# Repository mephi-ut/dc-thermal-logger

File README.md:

LICENSE: WTFPLv2

The purpose of this project is to monitor themperature in a lot of points of DC.

Operating principle:

Collector schematic:

Thermal sensor schematic:

A model photo:

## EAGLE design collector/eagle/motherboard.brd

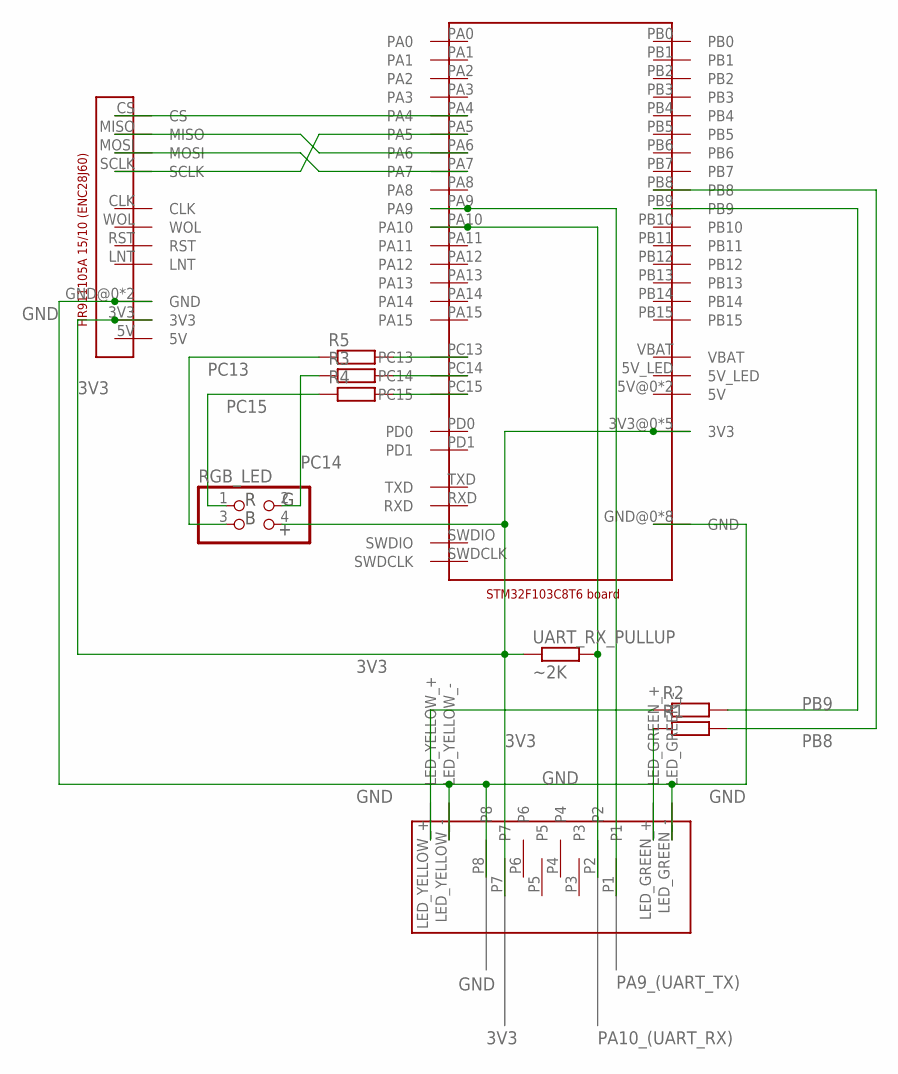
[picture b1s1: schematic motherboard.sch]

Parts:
R1, R2, R3, R4, R5: R-EU_R1206; R1206
RGB_LED: PINHD-2X2; 2X02
U$1: HANRUN_HR911105A_15/10
U$2: STM32F103C8T6_BOARD_BLACK
U$3: RJHSE-5481_(RJ45)
UART_RX_PULLUP: ~2K; R1206

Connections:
3V3: RGB_LED.4, U$1.3V3, U$2.3V3@0 (3V3), U$2.3V3@1 (3V3), U$2.3V3@2 (3V3), U$2.3V3@3 (3V3), U$2.3V3@4 (3V3), U$3.P7, UART_RX_PULLUP.1
GND: U$1.GND@0 (GND), U$1.GND@1 (GND), U$2.GND@0 (GND), U$2.GND@1 (GND), U$2.GND@2 (GND), U$2.GND@3 (GND), U$2.GND@4 (GND), U$2.GND@5 (GND), U$2.GND@6 (GND), U$2.GND@7 (GND), U$3.LED_GREEN_-, U$3.LED_YELLOW_-, U$3.P8
unnamed: U$1.CS, U$2.PA4
unnamed: U$1.SCLK, U$2.PA5
unnamed: U$1.MISO, U$2.PA6
unnamed: U$1.MOSI, U$2.PA7
unnamed: R1.1, U$3.LED_GREEN_+
unnamed: R4.2, U$2.PC15
unnamed: R3.2, U$2.PC14
unnamed: R5.2, U$2.PC13
PA9_(UART_TX): U$2.PA9, U$3.P1
PA10_(UART_RX): U$2.PA10, U$3.P2, UART_RX_PULLUP.2
PB8: R1.2, U$2.PB8
PB9: R2.2, U$2.PB9
PB9R: R2.1, U$3.LED_YELLOW_+
PC13: R5.1, RGB_LED.3
PC14: R3.1, RGB_LED.2
PC15: R4.1, RGB_LED.1

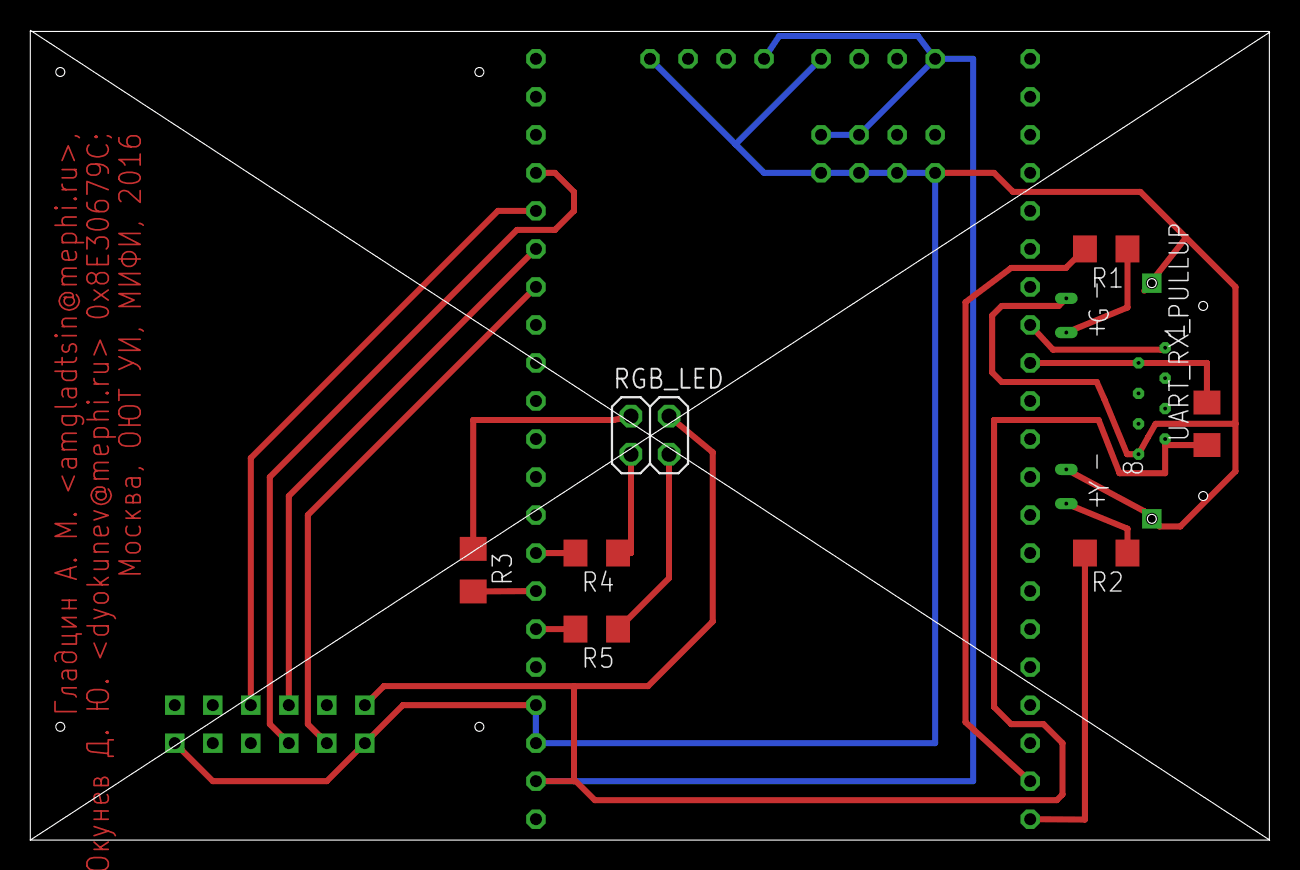
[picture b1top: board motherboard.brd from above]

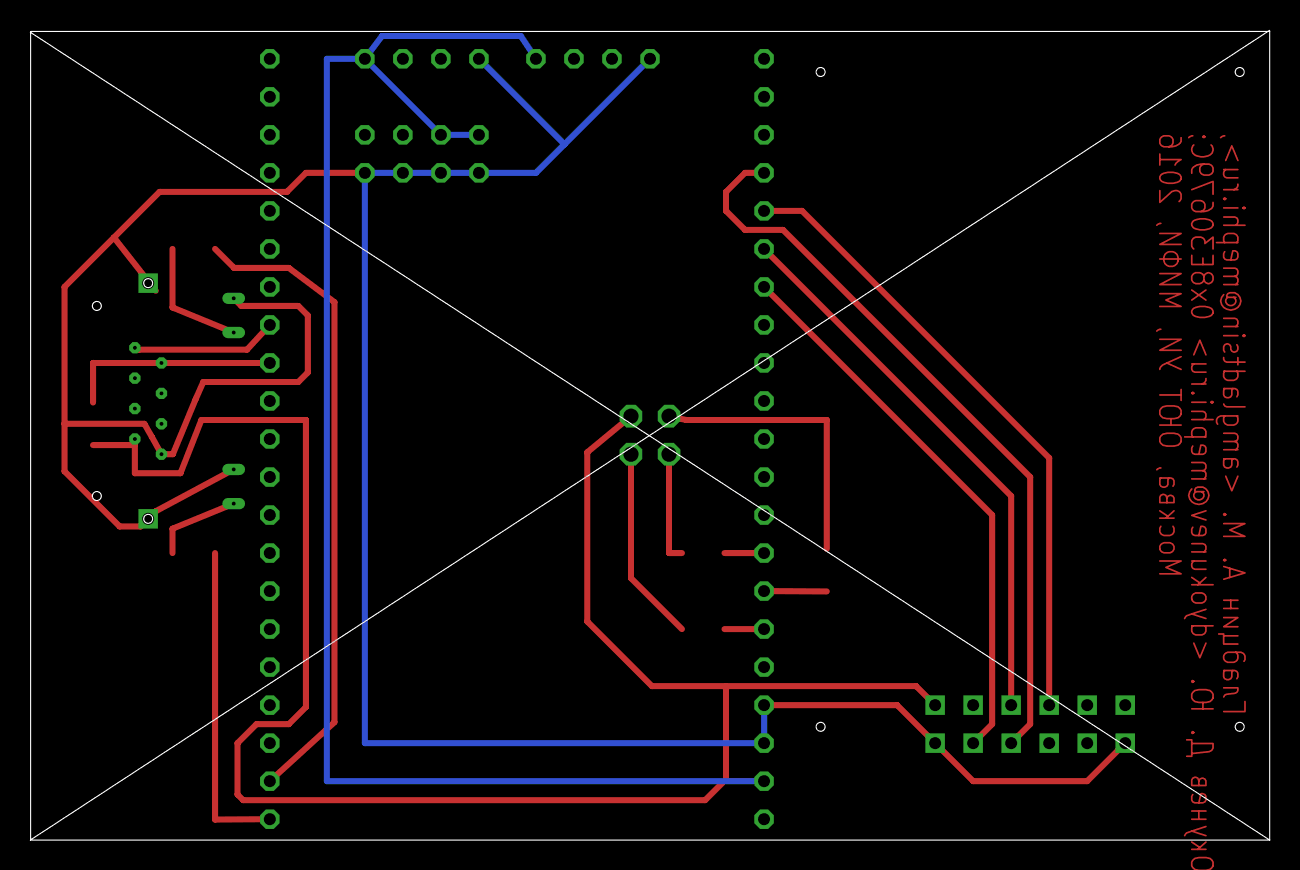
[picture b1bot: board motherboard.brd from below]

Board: 2 copper layers, 82.8 x 54.1 mm, 10 parts (2 on the bottom side), 18 nets.

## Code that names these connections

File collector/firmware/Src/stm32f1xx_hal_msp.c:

/**
  ******************************************************************************
  * File Name          : stm32f1xx_hal_msp.c
  * Description        : This file provides code for the MSP Initialization 
  *                      and de-Initialization codes.
  ******************************************************************************
  *
  * COPYRIGHT(c) 2016 STMicroelectronics
  *
  * Redistribution and use in source and binary forms, with or without modification,
  * are permitted provided that the following conditions are met:
  *   1. Redistributions of source code must retain the above copyright notice,
  *      this list of conditions and the following disclaimer.
  *   2. Redistributions in binary form must reproduce the above copyright notice,
  *      this list of conditions and the following disclaimer in the documentation
  *      and/or other materials provided with the distribution.
  *   3. Neither the name of STMicroelectronics nor the names of its contributors
  *      may be used to endorse or promote products derived from this software
  *      without specific prior written permission.
  *
  * THIS SOFTWARE IS PROVIDED BY THE COPYRIGHT HOLDERS AND CONTRIBUTORS "AS IS"
  * AND ANY EXPRESS OR IMPLIED WARRANTIES, INCLUDING, BUT NOT LIMITED TO, THE
  * IMPLIED WARRANTIES OF MERCHANTABILITY AND FITNESS FOR A PARTICULAR PURPOSE ARE
  * DISCLAIMED. IN NO EVENT SHALL THE COPYRIGHT HOLDER OR CONTRIBUTORS BE LIABLE
  * FOR ANY DIRECT, INDIRECT, INCIDENTAL, SPECIAL, EXEMPLARY, OR CONSEQUENTIAL
  * DAMAGES (INCLUDING, BUT NOT LIMITED TO, PROCUREMENT OF SUBSTITUTE GOODS OR
  * SERVICES; LOSS OF USE, DATA, OR PROFITS; OR BUSINESS INTERRUPTION) HOWEVER
  * CAUSED AND ON ANY THEORY OF LIABILITY, WHETHER IN CONTRACT, STRICT LIABILITY,
  * OR TORT (INCLUDING NEGLIGENCE OR OTHERWISE) ARISING IN ANY WAY OUT OF THE USE
  * OF THIS SOFTWARE, EVEN IF ADVISED OF THE POSSIBILITY OF SUCH DAMAGE.
  *
  ******************************************************************************
  */
/* Includes ------------------------------------------------------------------*/
#include "stm32f1xx_hal.h"

extern DMA_HandleTypeDef hdma_spi1_rx;

extern DMA_HandleTypeDef hdma_spi1_tx;

extern DMA_HandleTypeDef hdma_usart1_rx;

extern DMA_HandleTypeDef hdma_usart1_tx;

/* USER CODE BEGIN 0 */

/* USER CODE END 0 */

/**
  * Initializes the Global MSP.
  */
void HAL_MspInit(void)
{
  /* USER CODE BEGIN MspInit 0 */

  /* USER CODE END MspInit 0 */

  __HAL_RCC_AFIO_CLK_ENABLE();

  HAL_NVIC_SetPriorityGrouping(NVIC_PRIORITYGROUP_4);

  /* System interrupt init*/
  /* SysTick_IRQn interrupt configuration */
  HAL_NVIC_SetPriority(SysTick_IRQn, 0, 0);

    /**NOJTAG: JTAG-DP Disabled and SW-DP Enabled 
    */
  __HAL_AFIO_REMAP_SWJ_NOJTAG();

  /* USER CODE BEGIN MspInit 1 */

  /* USER CODE END MspInit 1 */
}

void HAL_SPI_MspInit(SPI_HandleTypeDef* hspi)
{

  GPIO_InitTypeDef GPIO_InitStruct;
  if(hspi->Instance==SPI1)
  {
  /* USER CODE BEGIN SPI1_MspInit 0 */

  /* USER CODE END SPI1_MspInit 0 */
    /* Peripheral clock enable */
    __SPI1_CLK_ENABLE();
  
    /**SPI1 GPIO Configuration    
    PA5     ------> SPI1_SCK
    PA6     ------> SPI1_MISO
    PA7     ------> SPI1_MOSI 
    */
    GPIO_InitStruct.Pin = GPIO_PIN_5|GPIO_PIN_7;
    GPIO_InitStruct.Mode = GPIO_MODE_AF_PP;
    GPIO_InitStruct.Speed = GPIO_SPEED_HIGH;
    HAL_GPIO_Init(GPIOA, &GPIO_InitStruct);

    GPIO_InitStruct.Pin = GPIO_PIN_6;
    GPIO_InitStruct.Mode = GPIO_MODE_INPUT;
    GPIO_InitStruct.Pull = GPIO_NOPULL;
    HAL_GPIO_Init(GPIOA, &GPIO_InitStruct);

    /* Peripheral DMA init*/
  
    hdma_spi1_rx.Instance = DMA1_Channel2;
    hdma_spi1_rx.Init.Direction = DMA_PERIPH_TO_MEMORY;
    hdma_spi1_rx.Init.PeriphInc = DMA_PINC_DISABLE;
    hdma_spi1_rx.Init.MemInc = DMA_MINC_ENABLE;
    hdma_spi1_rx.Init.PeriphDataAlignment = DMA_PDATAALIGN_BYTE;
    hdma_spi1_rx.Init.MemDataAlignment = DMA_MDATAALIGN_BYTE;
    hdma_spi1_rx.Init.Mode = DMA_NORMAL;
    hdma_spi1_rx.Init.Priority = DMA_PRIORITY_LOW;
    HAL_DMA_Init(&hdma_spi1_rx);

    __HAL_LINKDMA(hspi,hdmarx,hdma_spi1_rx);

    hdma_spi1_tx.Instance = DMA1_Channel3;
    hdma_spi1_tx.Init.Direction = DMA_MEMORY_TO_PERIPH;
    hdma_spi1_tx.Init.PeriphInc = DMA_PINC_DISABLE;
    hdma_spi1_tx.Init.MemInc = DMA_MINC_ENABLE;
    hdma_spi1_tx.Init.PeriphDataAlignment = DMA_PDATAALIGN_BYTE;
    hdma_spi1_tx.Init.MemDataAlignment = DMA_MDATAALIGN_BYTE;
    hdma_spi1_tx.Init.Mode = DMA_NORMAL;
    hdma_spi1_tx.Init.Priority = DMA_PRIORITY_LOW;
    HAL_DMA_Init(&hdma_spi1_tx);

    __HAL_LINKDMA(hspi,hdmatx,hdma_spi1_tx);

  /* USER CODE BEGIN SPI1_MspInit 1 */

  /* USER CODE END SPI1_MspInit 1 */
  }

}

void HAL_SPI_MspDeInit(SPI_HandleTypeDef* hspi)
{

  if(hspi->Instance==SPI1)
  {
  /* USER CODE BEGIN SPI1_MspDeInit 0 */

  /* USER CODE END SPI1_MspDeInit 0 */
    /* Peripheral clock disable */
    __SPI1_CLK_DISABLE();
  
    /**SPI1 GPIO Configuration    
    PA5     ------> SPI1_SCK
    PA6     ------> SPI1_MISO
    PA7     ------> SPI1_MOSI 
    */
    HAL_GPIO_DeInit(GPIOA, GPIO_PIN_5|GPIO_PIN_6|GPIO_PIN_7);

    /* Peripheral DMA DeInit*/
    HAL_DMA_DeInit(hspi->hdmarx);
    HAL_DMA_DeInit(hspi->hdmatx);
  }
  /* USER CODE BEGIN SPI1_MspDeInit 1 */

  /* USER CODE END SPI1_MspDeInit 1 */

}

void HAL_UART_MspInit(UART_HandleTypeDef* huart)
{

  GPIO_InitTypeDef GPIO_InitStruct;
  if(huart->Instance==USART1)
  {
  /* USER CODE BEGIN USART1_MspInit 0 */

  /* USER CODE END USART1_MspInit 0 */
    /* Peripheral clock enable */
    __USART1_CLK_ENABLE();
  
    /**USART1 GPIO Configuration    
    PA9     ------> USART1_TX
    PA10     ------> USART1_RX 
    */
    GPIO_InitStruct.Pin = GPIO_PIN_9;
    GPIO_InitStruct.Mode = GPIO_MODE_AF_PP;
    GPIO_InitStruct.Speed = GPIO_SPEED_HIGH;
    HAL_GPIO_Init(GPIOA, &GPIO_InitStruct);

    GPIO_InitStruct.Pin = GPIO_PIN_10;
    GPIO_InitStruct.Mode = GPIO_MODE_INPUT;
    GPIO_InitStruct.Pull = GPIO_NOPULL;
    HAL_GPIO_Init(GPIOA, &GPIO_InitStruct);

    /* Peripheral DMA init*/
  
    hdma_usart1_rx.Instance = DMA1_Channel5;
    hdma_usart1_rx.Init.Direction = DMA_PERIPH_TO_MEMORY;
    hdma_usart1_rx.Init.PeriphInc = DMA_PINC_DISABLE;
    hdma_usart1_rx.Init.MemInc = DMA_MINC_ENABLE;
    hdma_usart1_rx.Init.PeriphDataAlignment = DMA_PDATAALIGN_BYTE;
    hdma_usart1_rx.Init.MemDataAlignment = DMA_MDATAALIGN_BYTE;
    hdma_usart1_rx.Init.Mode = DMA_CIRCULAR;
    hdma_usart1_rx.Init.Priority = DMA_PRIORITY_LOW;
    HAL_DMA_Init(&hdma_usart1_rx);

    __HAL_LINKDMA(huart,hdmarx,hdma_usart1_rx);

    hdma_usart1_tx.Instance = DMA1_Channel4;
    hdma_usart1_tx.Init.Direction = DMA_MEMORY_TO_PERIPH;
    hdma_usart1_tx.Init.PeriphInc = DMA_PINC_DISABLE;
    hdma_usart1_tx.Init.MemInc = DMA_MINC_ENABLE;
    hdma_usart1_tx.Init.PeriphDataAlignment = DMA_PDATAALIGN_BYTE;
    hdma_usart1_tx.Init.MemDataAlignment = DMA_MDATAALIGN_BYTE;
    hdma_usart1_tx.Init.Mode = DMA_NORMAL;
    hdma_usart1_tx.Init.Priority = DMA_PRIORITY_LOW;
    HAL_DMA_Init(&hdma_usart1_tx);

    __HAL_LINKDMA(huart,hdmatx,hdma_usart1_tx);

  /* USER CODE BEGIN USART1_MspInit 1 */

  /* USER CODE END USART1_MspInit 1 */
  }

}

void HAL_UART_MspDeInit(UART_HandleTypeDef* huart)
{

  if(huart->Instance==USART1)
  {
  /* USER CODE BEGIN USART1_MspDeInit 0 */

  /* USER CODE END USART1_MspDeInit 0 */
    /* Peripheral clock disable */
    __USART1_CLK_DISABLE();
  
    /**USART1 GPIO Configuration    
    PA9     ------> USART1_TX
    PA10     ------> USART1_RX 
    */
    HAL_GPIO_DeInit(GPIOA, GPIO_PIN_9|GPIO_PIN_10);

    /* Peripheral DMA DeInit*/
    HAL_DMA_DeInit(huart->hdmarx);
    HAL_DMA_DeInit(huart->hdmatx);
  }
  /* USER CODE BEGIN USART1_MspDeInit 1 */

  /* USER CODE END USART1_MspDeInit 1 */

}

/* USER CODE BEGIN 1 */

/* USER CODE END 1 */

/**
  * @}
  */

/**
  * @}
  */

/************************ (C) COPYRIGHT STMicroelectronics *****END OF FILE****/

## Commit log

2016-06-22 Added initial tree for collector firmware
2016-06-22 It pings :)
    It pings, but very slow:
    round-trip min/avg/max/stddev = 543.156/4264.099/6096.301/592.690 ms
2016-06-22 Fixed problem with too slow ethernet; added some docs
2016-06-22 Added initial README.md
2016-06-22 Continued initial code
2016-06-22 Fixed UART Transmit
2016-06-23 Added initial skeleton for sensor firmware
2016-06-23 First communication success (but only on one slave)
2016-06-23 works: one slave -> collector -> server
2016-06-23 Added a workaround for ADC starting
2016-06-23 Fixed slaves to work on one bus
2016-06-24 Added motherboard board draft
2016-06-24 Updated scheme of collector motherboard
2016-06-24 Tiny fixes on colletor's motherboard
2016-06-24 Updated sensor's scheme, colletor's photo and README.md
2016-06-24 Added a pull-up resistor for UART-RX of collector
2016-06-24 Updated screenshot of collector's scheme
2016-06-24 Added license clarification
2016-06-24 Started to implement server-side parser
2016-06-26 Complete initial log parser (udp->postgres)
2016-06-26 Removed extra "as" from log-parser
2016-06-26 Started the website
2016-06-26 Updated .gitignore
2016-06-27 Updated models in parser
2016-06-27 Updated models on server side
2016-06-27 Removed extra argument to Select()
2016-06-27 Added basic 2d map on http site
2016-06-27 Continued work on http site
2016-06-28 Almost production ready for one channel per sensor
2016-06-28 Added 5minutes aggregation
2016-06-28 Fixed the first rack array
2016-06-28 Changed theme to white
2016-06-28 Auto select sensor if it is alone in a group
2016-06-28 Made chart configurable
2016-06-28 Added chart export button
2016-07-02 Added first two serverRack sensor groups
2016-07-02 Switched to per minute aggregation
2016-07-02 Don't select minute-aggregated values with too shoal counter value
2016-07-03 Added more info for Nagios
2016-07-04 polishing
2016-07-05 Few fixes
    * Don't parse raw history in DevMode
    * Minimal temperature = 10
    * Preserve displaying sensor after page refresh
2016-07-05 Autoupdate data on screen
2016-07-06 Fixed dynamic updating
2016-07-06 no comment
2016-07-06 Added mobile version
2016-07-06 Added minimal version - "/m"
2016-07-06 Made "minimal" version more minimalistic
2016-07-06 Added sensor names to minimal version
2016-07-06 [minimal] Preserve conditionings names on update
2016-07-06 [mobile] Added different colors for different statuses
2016-07-08 Fixed firmwares
2016-07-11 Fixed compiling collector in ICMP echo server mode
2016-07-13 Disabled optimizations (bugfix)
2016-07-25 Few bugfixes
2016-07-26 Updated "reform" for models
2016-07-26 Added logout button
2016-07-26 Added old-fashion authorization (for backward compatibility)
2016-07-27 Added reserve DC
2016-10-08 Don't remember
2016-10-08 Migrated to MySQL due to performance issues
2016-10-08 [site] Select feasible raw records at once
2016-11-02 Added 10 seconds cache for main page
2016-11-02 Completed migration to mysql
2016-12-14 Disabled sensor 77
